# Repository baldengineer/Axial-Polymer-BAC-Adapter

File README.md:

## KiCad Design files for Axial Polymer BAC Adapter
Vintage computers, video game systems, and electronics tend to use very large decoupling capacitors. You can find them next to linear regulators, like the venrable LM7805. Often if the cap is more than 1,000 uF, it is an axial form factor.

Axial form factor means the leads or electrodes come out of the "top" and "bottom" of the capacitor, allowing it to be laid-down on the PCB. This reduces the height.

Unfortuantely, no manufacturer today makes polymer aluminum electrolytics in a axial form factor. These are my preferred capacitor for re-capping since they have significantly lower-ESR and are solid. So there is no electrolyte to ever leak-out and damage the cirucit boards.

The Axial Polymer BAC-Adapter converts modern surface mount polymers into a vintage axial format. 

The size of this design is 53.4 x 13.1 mm and can hold 4 10x10.5 mm surface mount capacitors. It should fit in a VIC-20 and Commodore 64. (Still need to test.)

Tested boards came back (and are beautiful). They work well!

## Bald Engineer on Twitch
This board was designed, built, and tested live with the Bald Engineer. Check out his electronics live stream at: https://twitch.tv/baldengineer.

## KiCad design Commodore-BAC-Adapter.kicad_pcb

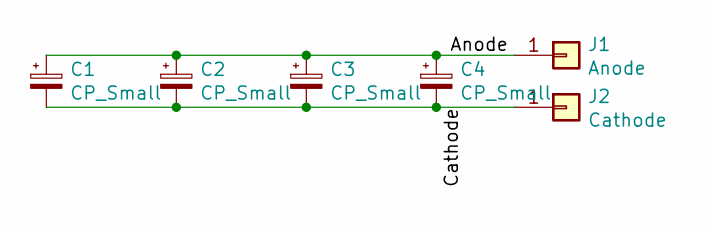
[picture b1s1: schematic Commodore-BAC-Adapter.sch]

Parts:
C1, C2, C3, C4: CP_Small; CP_Elec_10x10.5-Modified_Silk
J1: Anode; Slot-Conn_1x1
J2: Cathode; Slot-Conn_1x1

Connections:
/Anode: C1.1, C2.1, C3.1, C4.1, J1.1
/Cathode: C1.2, C2.2, C3.2, C4.2, J2.1

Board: 2 copper layers, 6 parts (0 on the bottom side), 2 nets, no tracks yet.

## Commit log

2020-10-10 v1 of the pcb
2020-11-08 Board function tested
